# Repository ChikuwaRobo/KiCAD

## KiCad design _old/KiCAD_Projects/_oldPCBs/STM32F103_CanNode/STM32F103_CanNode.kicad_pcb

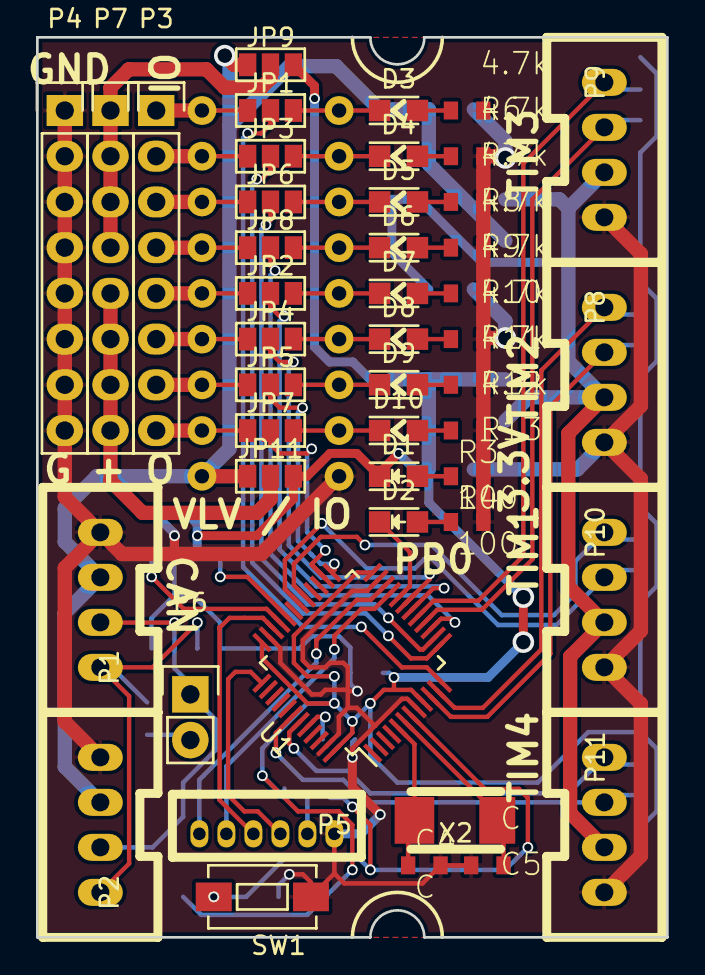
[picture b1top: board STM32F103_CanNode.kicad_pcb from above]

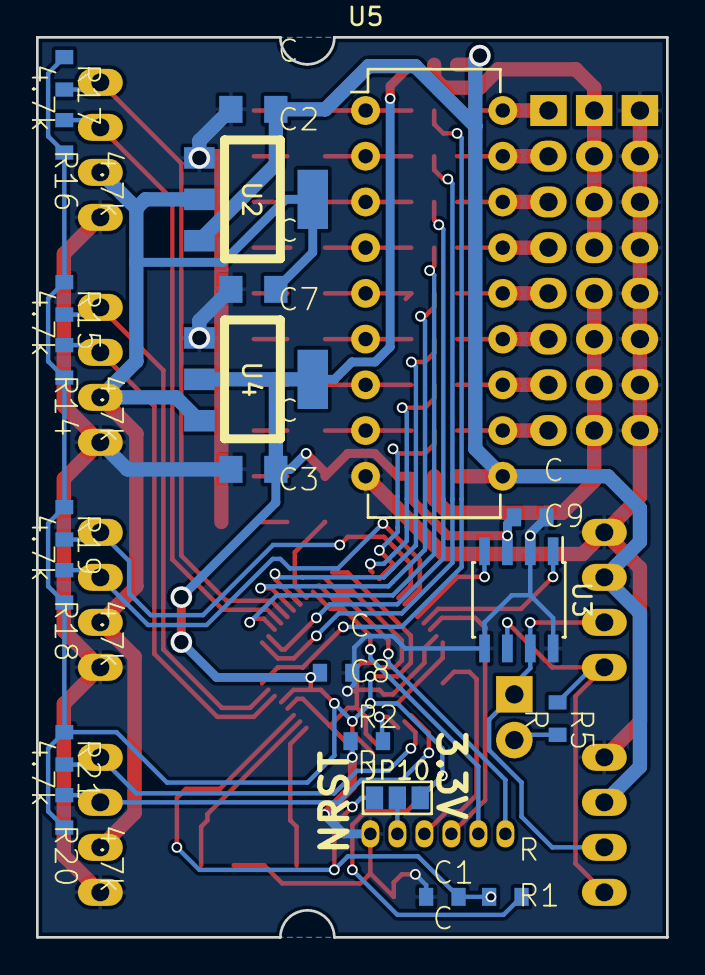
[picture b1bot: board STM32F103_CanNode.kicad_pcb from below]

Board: 2 copper layers, 35.0 x 50.0 mm, 68 parts (22 on the bottom side), 63 nets.

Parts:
C1, C4, C5, C8, C9: C; C1608_WP
C2, C3, C7: C; C2012
D1, D2, D3, D4, D5, D6, D7, D8, D9, D10: LED; LED_0805
JP1, JP2, JP3, JP4, JP5, JP6, JP7, JP8, JP9, JP10, JP11: JUMPER3; GS3
P1, P2, P8, P9, P10, P11: CONN_01X04; XA_4T
P3, P4, P7: CONN_01X08; Pin_Header_Straight_1x08
P5: CONN_01X06; ZH_6T
P6: CONN_01X02; Pin_Header_Straight_1x02
R1, R2, R5: R; C1608_WP
R3, R4: 100; C1608_WP
R6, R7, R8, R9, R10, R11, R12, R13, R14, R15, R16, R17, R18, R19, R20, R21: 4.7k; C1608_WP
SW1: SW_PUSH; SW_SPST_EVQPE1
U1: STM32F103_48; LQFP-48_7x7mm_Pitch0.5mm
U2: NCP1117ST33T3G; SOT-223_reg
U3: MAX3051; SOIC-8_3.9x4.9mm_Pitch1.27mm
U4: NCP1117ST50T3G; SOT-223_reg
U5: TBD62083A; DIP-18_W7.62mm
X2: CRYSTAL; ABM3_2pads

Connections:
+3.3V: C3.1, C8.2, C9.2, D1.1, JP9.3, JP10.3, JP11.3, R1.1, R14.1, R15.1, R16.1, R17.1, R18.1, R19.1, R20.1, R21.1, U1.9, U1.24, U1.36, U1.48, U3.3, U4.2
+5V: C7.1, P8.2, P9.2, P10.2, P11.2, U2.2, U4.3
+12V: C2.1, JP9.1, JP11.1, P1.2, P2.2, U2.3, U5.10
/BOOT0: R2.2, U1.44
/CAN_H: P1.3, P2.3, P6.1, U3.7
/CAN_L: P1.4, P2.4, R5.1, U3.6
/CAN_RX: U1.32, U3.4
/CAN_TX: U1.33, U3.1
/IO1: JP1.1, P3.1, U5.18
/IO2: JP3.1, P3.2, U5.17
/IO3: JP6.1, P3.3, U5.16
/IO4: JP8.1, P3.4, U5.15
/IO5: JP2.1, P3.5, U5.14
/IO6: JP4.1, P3.6, U5.13
/IO7: JP5.1, P3.7, U5.12
/IO8: JP7.1, P3.8, U5.11
/NRST: C1.2, JP10.1, R1.2, SW1.2, U1.7
/OSC_IN: C4.1, U1.5, X2.1
/OSC_OUT: C5.1, U1.6, X2.2
/OUT1: D3.1, JP1.3, U5.1
/OUT2: D4.1, JP3.3, U5.2
/OUT3: D5.1, JP6.3, U5.3
/OUT4: D6.1, JP8.3, U5.4
/OUT5: D7.1, JP2.3, U5.5
/OUT6: D8.1, JP4.3, U5.6
/OUT7: D9.1, JP5.3, U5.7
/OUT8: D10.1, JP7.3, U5.8
/PA0: P8.3, R14.2, U1.10
/PA1: P8.4, R15.2, U1.11
/PA2: JP1.2, U1.12
/PA3: JP3.2, U1.13
/PA4: JP6.2, U1.14
/PA5: JP8.2, U1.15
/PA6: P9.3, R16.2, U1.16
/PA7: P9.4, R17.2, U1.17
/PA8: P10.4, R19.2, U1.29
/PA9: P10.3, R18.2, U1.30
/PB0: JP2.2, U1.18
/PB1: JP4.2, U1.19
/PB2: D2.1, U1.20
/PB6: P11.3, R20.2, U1.42
/PB7: P11.4, R21.2, U1.43
/PB12: JP5.2, U1.25
/PB13: JP7.2, U1.26
/SWCLK: P5.3, U1.37
/SWDIO: P5.4, U1.34
/USART_RX: P5.6, U1.22
/USART_TX: P5.5, U1.21
GND: C1.1, C2.2, C3.2, C4.2, C5.2, C7.2, C8.1, C9.1, P1.1, P2.1, P4.1, P4.2, P4.3, P4.4, P4.5, P4.6, P4.7, P4.8, P5.1, P8.1, P9.1, P10.1, P11.1, R2.1, R3.2, R4.2, R6.1, R7.1, R8.1, R9.1, R10.1, R11.1, R12.1, R13.1, SW1.1, U1.8, U1.23, U1.35, U1.47, U2.1, U3.2, U3.5, U3.8, U4.1, U5.9
unnamed: D1.2, R3.1
unnamed: D2.2, R4.1
unnamed: D3.2, R6.2
unnamed: D4.2, R7.2
unnamed: D5.2, R8.2
unnamed: D6.2, R9.2
unnamed: D7.2, R10.2
unnamed: D8.2, R11.2
unnamed: D9.2, R12.2
unnamed: D10.2, R13.2
unnamed: JP9.2, P7.1, P7.2, P7.3, P7.4
unnamed: JP10.2, P5.2
unnamed: JP11.2, P7.5, P7.6, P7.7, P7.8
unnamed: P6.2, R5.2

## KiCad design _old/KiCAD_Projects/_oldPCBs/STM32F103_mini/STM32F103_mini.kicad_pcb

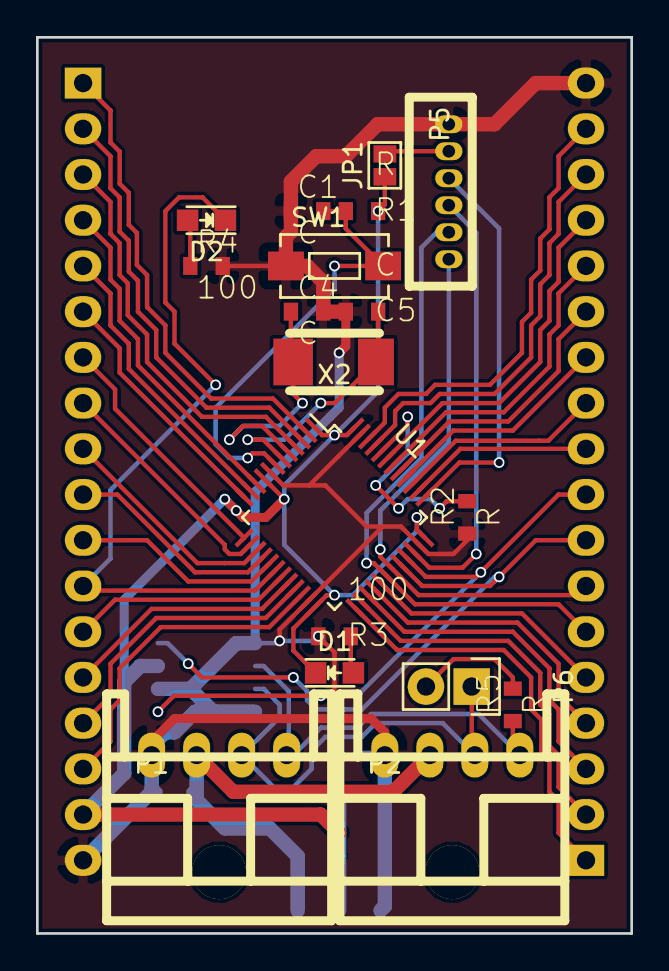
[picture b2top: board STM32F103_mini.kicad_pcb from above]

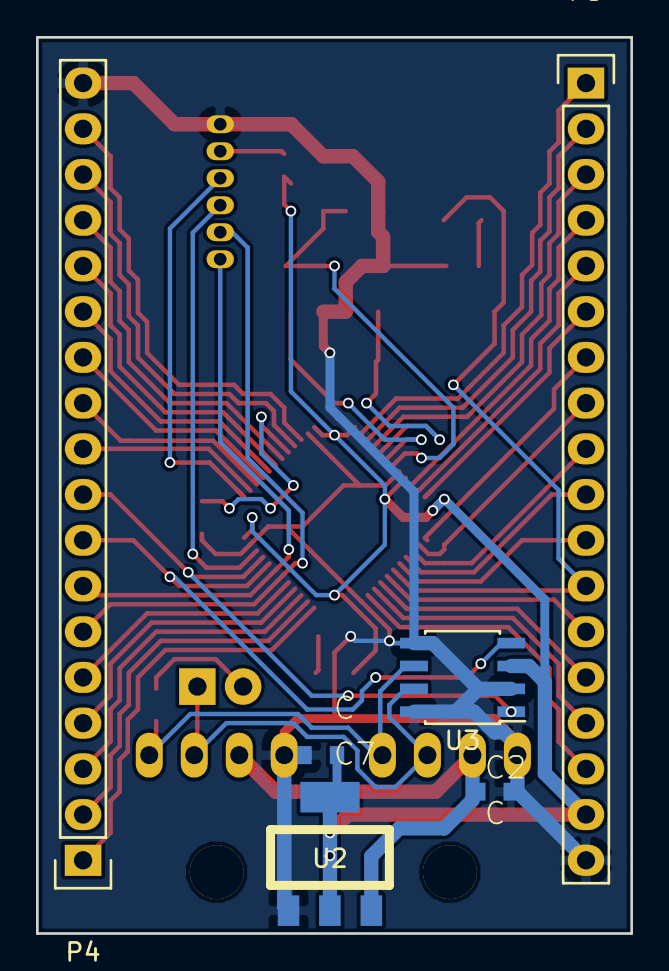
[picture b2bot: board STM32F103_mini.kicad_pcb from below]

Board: 2 copper layers, 33.0 x 49.8 mm, 24 parts (6 on the bottom side), 48 nets.

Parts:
C1, C2, C4, C5, C7: C; C1608_WP
D1, D2: LED; LED_0805
JP1: JUMPER; GS2
P1, P2: CONN_01X04; XA_4LC
P3, P4: CONN_01X18; Pin_Header_Straight_1x18
P5: CONN_01X06; ZH_6T
P6: CONN_01X02; Pin_Header_Straight_1x02
R1, R2, R5: R; C1608_WP
R3, R4: 100; C1608_WP
SW1: SW_PUSH; SW_SPST_EVQPE1
U1: STM32F103_48; LQFP-48_7x7mm_Pitch0.5mm
U2: NCP1117ST33T3G; SOT-223_reg
U3: MAX3051; SOIC-8_3.9x4.9mm_Pitch1.27mm
X2: CRYSTAL; ABM3_2pads

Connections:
+3V3: C7.1, D1.1, JP1.1, P3.17, R1.1, U1.1, U1.9, U1.24, U1.36, U1.48, U2.2, U3.3
+12V: C2.1, P1.2, P2.2, U2.3
/BOOT0: R2.2, U1.44
/CAN_H: P1.3, P2.3, P6.1, U3.7
/CAN_L: P1.4, P2.4, R5.1, U3.6
/CAN_RX: P4.8, U1.32, U3.4
/CAN_TX: P4.9, U1.33, U3.1
/LED: D2.1, P3.12, U1.18
/NRST: C1.2, R1.2, SW1.2, U1.7
/OSC_IN: C4.1, U1.5, X2.1
/OSC_OUT: C5.1, U1.6, X2.2
/PA0: P3.4, U1.10
/PA1: P3.5, U1.11
/PA2: P3.6, U1.12
/PA3: P3.7, U1.13
/PA4: P3.8, U1.14
/PA5: P3.9, U1.15
/PA6: P3.10, U1.16
/PA7: P3.11, U1.17
/PA8: P4.5, U1.29
/PA15: P4.10, U1.38
/PB1: P3.13, U1.19
/PB2: P3.14, U1.20
/PB3: P4.11, U1.39
/PB4: P4.12, U1.40
/PB5: P4.13, U1.41
/PB6: P4.14, U1.42
/PB7: P4.15, U1.43
/PB8: P4.16, U1.45
/PB9: P4.17, U1.46
/PB10: P3.15, U1.21
/PB11: P3.16, U1.22
/PB12: P4.1, U1.25
/PB13: P4.2, U1.26
/PB14: P4.3, U1.27
/PB15: P4.4, U1.28
/PC13: P3.1, U1.2
/PC14: P3.2, U1.3
/PC15: P3.3, U1.4
/SWCLK: P5.3, U1.37
/SWDIO: P5.4, U1.34
/USART_RX: P4.7, P5.6, U1.31
/USART_TX: P4.6, P5.5, U1.30
GND: C1.1, C2.2, C4.2, C5.2, C7.2, P1.1, P2.1, P3.18, P4.18, P5.1, R2.1, R3.2, R4.2, SW1.1, U1.8, U1.23, U1.35, U1.47, U2.1, U3.2, U3.5, U3.8
unnamed: D1.2, R3.1
unnamed: D2.2, R4.1
unnamed: JP1.2, P5.2
unnamed: P6.2, R5.2

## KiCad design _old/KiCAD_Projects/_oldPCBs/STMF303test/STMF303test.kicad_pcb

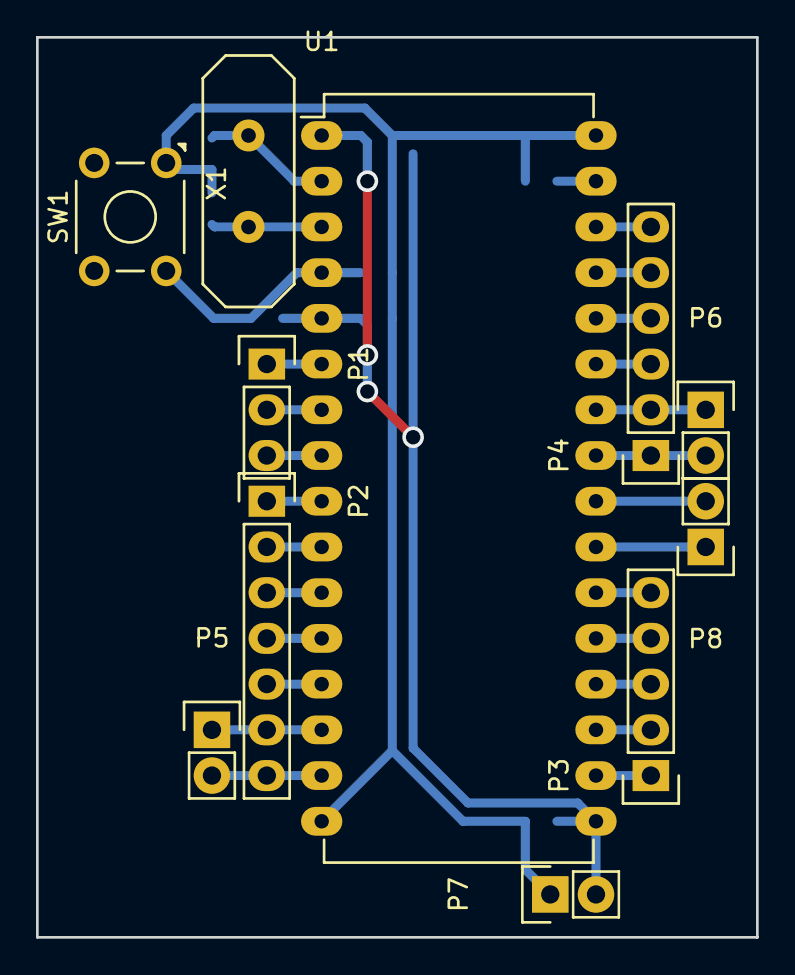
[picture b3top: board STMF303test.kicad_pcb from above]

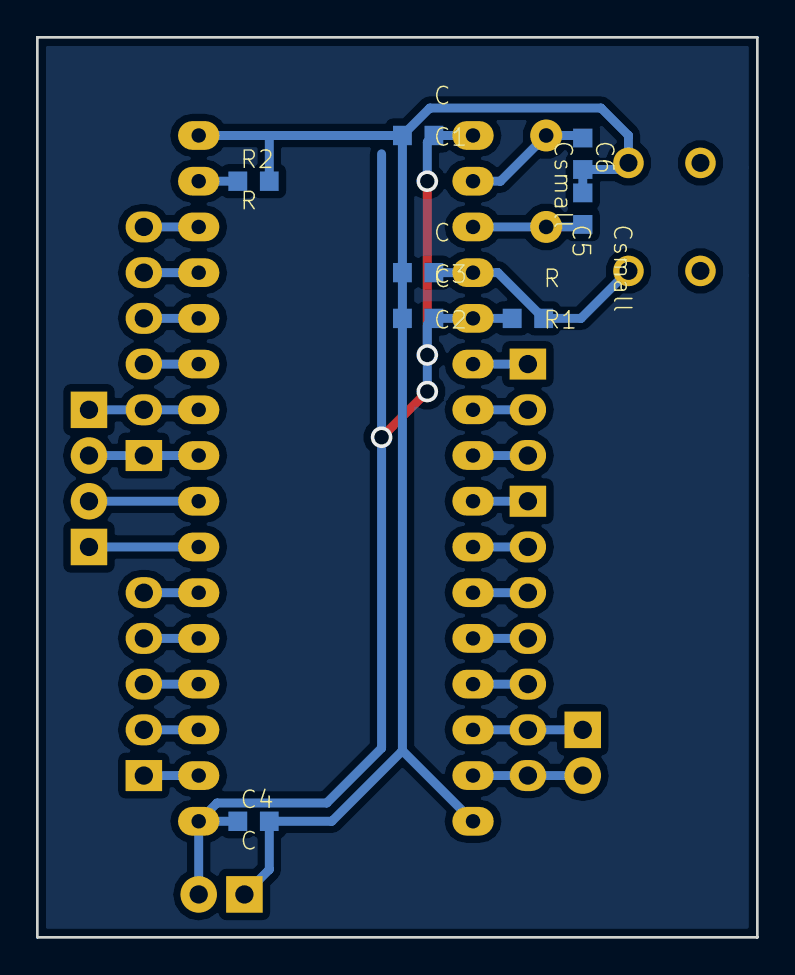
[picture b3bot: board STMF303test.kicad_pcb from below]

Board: 2 copper layers, 40.0 x 50.0 mm, 19 parts (8 on the bottom side), 29 nets.

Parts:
C1, C2, C3, C4: C; C0603K
C5, C6: Csmall; C0603K
P1: CONN_01X03; Socket_Strip_Straight_1x03
P2: CONN_01X07; Socket_Strip_Straight_1x07
P3: CONN_01X05; Socket_Strip_Straight_1x05
P4: CONN_01X06; Socket_Strip_Straight_1x06
P5, P6, P7, P8: CONN_01X02; Pin_Header_Straight_1x02
R1, R2: R; C0603K
SW1: SW_PUSH; SW_TH_Tactile_Omron_B3F-10xx
U1: STM32F303K8; DIP-32_W15.24mm_LongPads
X1: CRYSTAL; HC-18UV

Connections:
+3.3V: C1.1, C2.1, C4.1, P7.2, R1.2, U1.1, U1.5, U1.17
/PIN6: P1.1, U1.6
/PIN7: P1.2, U1.7
/PIN8: P1.3, U1.8
/PIN9: P2.1, U1.9
/PIN10: P2.2, U1.10
/PIN11: P2.3, U1.11
/PIN12: P2.4, U1.12
/PIN13: P2.5, U1.13
/PIN14: P2.6, P5.1, U1.14
/PIN15: P2.7, P5.2, U1.15
/PIN18: P3.1, U1.18
/PIN19: P3.2, U1.19
/PIN20: P3.3, U1.20
/PIN21: P3.4, U1.21
/PIN22: P3.5, U1.22
/PIN25: P4.1, P6.2, U1.25
/PIN26: P4.2, P6.1, U1.26
/PIN27: P4.3, U1.27
/PIN28: P4.4, U1.28
/PIN29: P4.5, U1.29
/PIN30: P4.6, U1.30
/SWCLK: P8.2, U1.24
/SWDIO: P8.1, U1.23
GND: C1.2, C2.2, C3.2, C4.2, C5.2, C6.2, P7.1, R2.2, SW1.1, U1.16, U1.32
unnamed: C3.1, R1.1, SW1.2, U1.4
unnamed: C5.1, U1.3, X1.1
unnamed: C6.1, U1.2, X1.2
unnamed: R2.1, U1.31

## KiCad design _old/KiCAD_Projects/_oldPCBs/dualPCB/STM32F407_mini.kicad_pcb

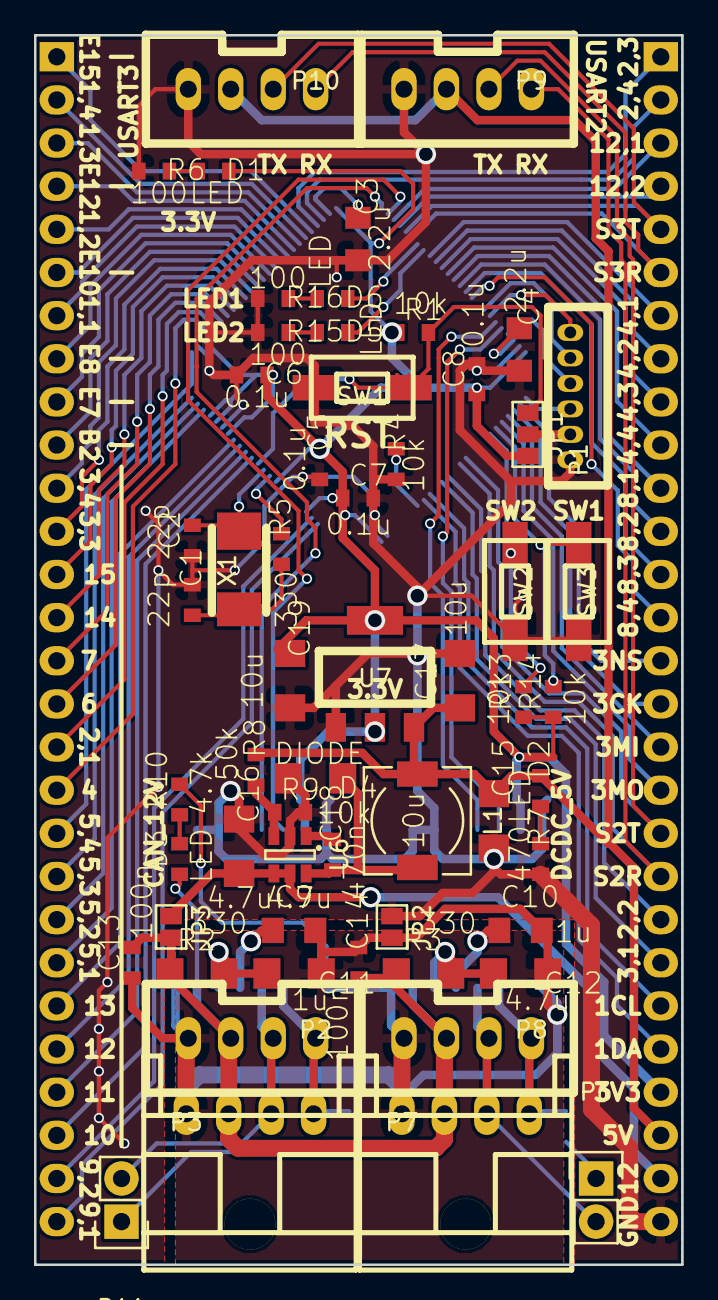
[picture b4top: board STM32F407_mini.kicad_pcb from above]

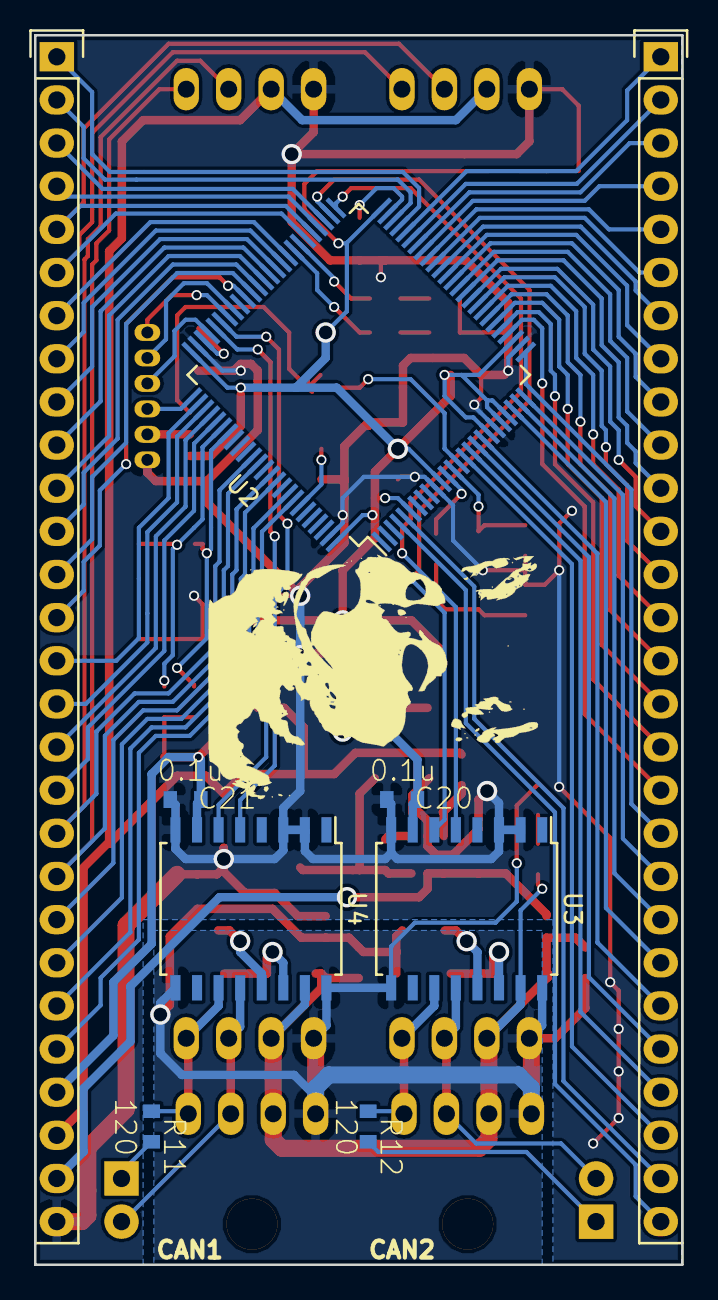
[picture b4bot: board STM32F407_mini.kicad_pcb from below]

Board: 2 copper layers, 38.1 x 72.4 mm, 67 parts (9 on the bottom side), 96 nets.

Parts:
C1, C2: 22p; C1608_WP
C3, C4: 2.2u; C2012
C5, C6, C7, C8, C20, C21: 0.1u; C1608_WP
C9, C10: 1u; C2012
C11, C12, C16: 4.7u; C3216
C13, C14: 100n; C1608_WP
C15, C17, C19: 10u; C3216
C18: 470n; C1608_WP
D1, D2, D3, D5, D6: LED; C1608_WP
D4: DIODE; C3216
JP1: JUMPER3; GS3
JP2, JP3: JUMPER; GS2
L1: 2.2uH; Choke_SMD_6.3x6.3_H3
P1: CONN_01X06; ZH_6T
P2, P8, P9, P10: CONN_01X04; XA_4T
P3, P7: CONN_01X04; XA_4LC
P4, P5: CONN_01X28; Pin_Header_Straight_1x28
P6, P11: CONN_01X02; Pin_Header_Straight_1x02
R1, R4, R9, R13, R14: 10k; C1608_WP
R2, R3: 330; C3216
R5: 330; C1608_WP
R6, R15, R16: 100; C1608_WP
R7: 470; C1608_WP
R8: 50k; C1608_WP
R10: 4.7k; C1608_WP
R11, R12: 120; C1608_WP
SW1, SW2, SW3: SW_PUSH; RP_SMD_Button
U2: STM32F407VG; LQFP-100_14x14mm_Pitch0.5mm
U3, U4: ADM3052; SOIC-16_7.5x10.3mm_Pitch1.27mm
U6: AOZ1280; SOT-23-6
U7: NCP1117ST33T3G; SOT-223_reg
X1: CRYSTAL; ABM3_2pads

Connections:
+3.3V: C5.1, C6.1, C7.1, C8.1, C19.1, C20.1, C21.1, D1.1, JP1.3, P5.25, R1.1, R13.1, R14.1, U2.6, U2.11, U2.19, U2.21, U2.22, U2.28, U2.50, U2.75, U2.100, U3.7, U4.7, U7.2
+5V: C15.1, C17.1, D2.1, L1.1, P5.26, P9.2, P10.2, R8.1, U7.3
+12V: C16.2, JP3.1, P5.27, U6.4, U6.5
/ADC1_6: P4.16, U2.31
/ADC1_7: P4.15, U2.32
/ADC1_IN4: P4.18, U2.29
/ADC_IN10: P4.26, U2.15
/ADC_IN11: P4.25, U2.16
/ADC_IN12: P4.24, U2.17
/ADC_IN13: P4.23, U2.18
/ADC_IN14: P4.14, U2.33
/ADC_IN15: P4.13, U2.34
/BOOT0: R4.1, U2.94
/CAN1_H: P6.2, P7.3, P8.3, U4.12
/CAN1_L: P7.4, P8.4, R11.1, U4.11
/CAN1_RX: U2.70, U4.5
/CAN1_TX: U2.71, U4.6
/CAN2_H: P2.3, P3.3, P11.2, U3.12
/CAN2_L: P2.4, P3.4, R12.1, U3.11
/CAN2_RX: U2.51, U3.5
/CAN2_TX: U2.52, U3.6
/CAN_12V: C13.2, C14.2, D3.1, JP3.2, P2.2, P3.2, P7.2, P8.2, R2.1, R3.1, U3.15, U4.15
/DCDC_FB: R8.2, R9.1, U6.3
/GPIO_PB2: P4.10, U2.37
/GPIO_PE7: P4.9, U2.38
/GPIO_PE8: P4.8, U2.39
/GPIO_PE10: P4.6, U2.41
/GPIO_PE12: P4.4, U2.43
/GPIO_PE15: P4.1, U2.46
/I2C1_SCL: P5.23, U2.92
/I2C1_SDA: P5.24, U2.93
/LED1: D6.1, U2.57
/LED2: D5.1, U2.58
/NRST: JP1.1, R1.2, SW1.1, U2.14
/SPI3_MISO: P5.17, U2.79
/SPI3_MOSI: P5.18, U2.80
/SPI3_NSS: P5.15, U2.77
/SPI3_SCK: P5.16, U2.78
/SW1_IN: R14.2, SW3.1, U2.81
/SW2_IN: R13.2, SW2.1, U2.82
/SWDCK: P1.3, U2.76
/SWDIO: P1.4, U2.72
/TIM1_CH1: P4.7, U2.40
/TIM1_CH2: P4.5, U2.42
/TIM1_CH3: P4.3, U2.44
/TIM1_CH4: P4.2, U2.45
/TIM2_CH1: P4.17, U2.30
/TIM2_CH2: P5.21, U2.89
/TIM2_CH3: P5.1, U2.47
/TIM2_CH4: P5.2, U2.48
/TIM3_CH1: P5.22, U2.90
/TIM3_CH3: P4.12, U2.35
/TIM3_CH4: P4.11, U2.36
/TIM4_CH1: P5.7, U2.59
/TIM4_CH2: P5.8, U2.60
/TIM4_CH3: P5.9, U2.61
/TIM4_CH4: P5.10, U2.62
/TIM5_CH1: P4.22, U2.23
/TIM5_CH2: P4.21, U2.24
/TIM5_CH3: P4.20, U2.25
/TIM5_CH4: P4.19, U2.26
/TIM8_CH1: P5.11, U2.63
/TIM8_CH2: P5.12, U2.64
/TIM8_CH3: P5.13, U2.65
/TIM8_CH4: P5.14, U2.66
/TIM9_CH1: P4.28, U2.4
/TIM9_CH2: P4.27, U2.5
/TIM12_CH1: P5.3, U2.53
/TIM12_CH2: P5.4, U2.54
/USART1_RX: P1.6, U2.69
/USART1_TX: P1.5, U2.68
/USART2_RX: P5.20, P9.4, U2.87
/USART2_TX: P5.19, P9.3, U2.86
/USART3_RX: P5.6, P10.4, U2.56
/USART3_TX: P5.5, P10.3, U2.55
DGND: C9.2, C10.2, C11.1, C12.1, C13.1, C14.1, JP2.2, P2.1, P3.1, P7.1, P8.1, R10.2, U3.9, U3.16, U4.9, U4.16
GND: C1.1, C2.1, C3.2, C4.2, C5.2, C6.2, C7.2, C8.2, C15.2, C16.1, C17.2, C19.2, C20.2, C21.2, D4.2, JP2.1, P1.1, P5.28, P9.1, P10.1, R4.2, R6.2, R7.2, R9.2, R15.2, R16.2, SW1.2, SW2.2, SW3.2, U2.10, U2.20, U2.27, U2.74, U2.99, U3.2, U3.3, U3.8, U4.2, U4.3, U4.8, U6.2, U7.1
unnamed: C1.2, R5.2, X1.2
unnamed: C2.2, U2.13, X1.1
unnamed: C3.1, U2.49
unnamed: C4.1, U2.73
unnamed: C9.1, U3.13
unnamed: C10.1, U4.13
unnamed: C11.2, R2.2, U3.14
unnamed: C12.2, R3.2, U4.14
unnamed: C18.1, U6.1
unnamed: C18.2, D4.1, L1.2, U6.6
unnamed: D1.2, R6.1
unnamed: D2.2, R7.1
unnamed: D3.2, R10.1
unnamed: D5.2, R15.1
unnamed: D6.2, R16.1
unnamed: JP1.2, P1.2
unnamed: P6.1, R11.2
unnamed: P11.1, R12.2
unnamed: R5.1, U2.12

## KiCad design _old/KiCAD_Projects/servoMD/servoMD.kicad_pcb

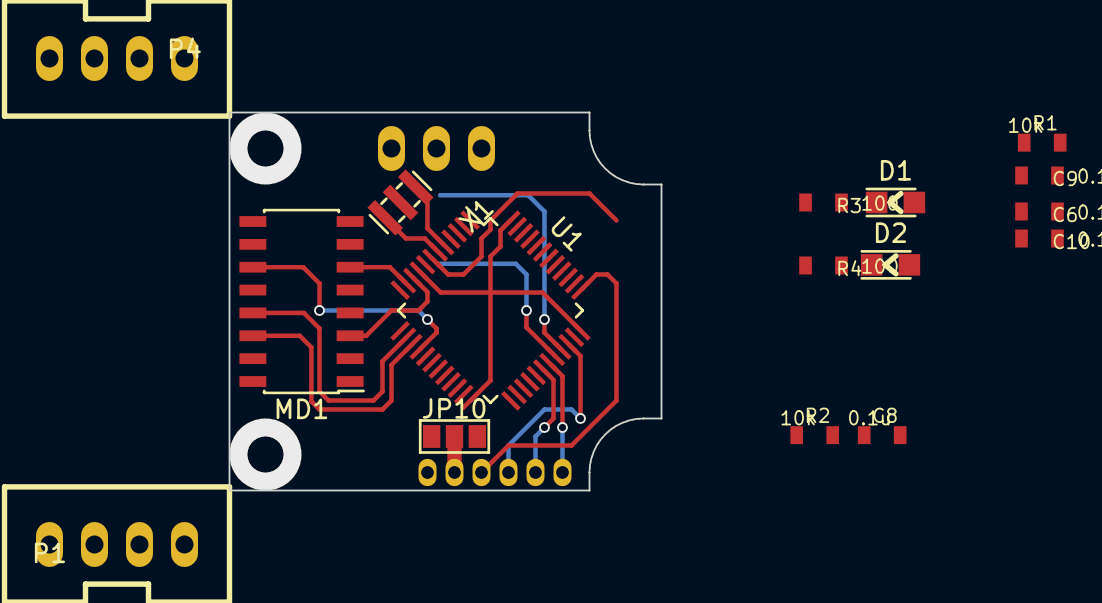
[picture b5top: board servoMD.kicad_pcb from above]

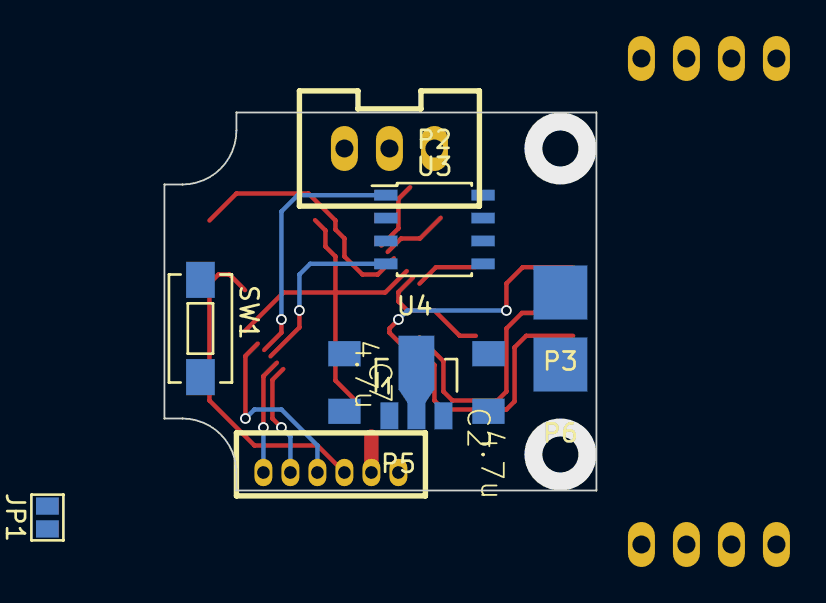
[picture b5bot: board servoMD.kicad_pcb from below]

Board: 2 copper layers, 24.0 x 21.0 mm, 26 parts (10 on the bottom side), 28 nets.

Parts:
C2, C7: 4.7u; C3216_S
C6, C8, C9, C10: 0.1u; C1608_WP_S
D1, D2: LED; LED_0805
JP1: JUMPER; GS2
JP10: JUMPER3; GS3
MD1: VNH7100AS; SOIC-16_3.9x9.9mm_Pitch1.27mm
P1, P4: CONN_01X04; XA_4T
P2: CONN_01X03; XA_3T
P3, P6: CONN_01X01; Measurement_Point_Square-SMD-Pad_Big
P5: CONN_01X06; ZH_6T
R1, R2: 10k; C1608_WP_S
R3, R4: 100; C1608_WP_S
SW1: SW_PUSH; SW_SPST_EVQPE1
U1: STM32F103_48; LQFP-48_7x7mm_Pitch0.5mm
U3: MAX3051; SOIC-8_3.9x4.9mm_Pitch1.27mm_S
U4: NCP1117ST50T3G; SOT89-3_Housing
X1: ceralock; Resonator_3×1.3mm

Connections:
+3.3V: C6.2, C7.1, C8.2, C9.2, C10.2, D1.1, JP10.3, P2.2, R1.1, U1.9, U1.24, U1.36, U1.48, U3.3, U4.2
+5V: JP10.1, P1.2
+12V: C2.1, MD1.4, MD1.5, MD1.12, U4.3
/BOOT0: R2.2, U1.44
/CAN_H: P4.3, U3.7
/CAN_L: P4.4, U3.6
/CAN_RX: U1.32, U3.4
/CAN_TX: U1.33, U3.1
/CS: MD1.13, U1.14
/INA: MD1.3, U1.10
/INB: MD1.6, U1.11
/NRST: R1.2, SW1.2, U1.7
/OSC_IN: U1.5, X1.1
/OSC_OUT: U1.6, X1.3
/OUTA: MD1.2, MD1.15, P3.1
/OUTB: MD1.7, MD1.10, P6.1
/POT: P2.3, U1.12
/PWM: MD1.11, U1.16
/SEL: MD1.14, U1.15
/SWCLK: P5.3, U1.37
/SWDIO: P5.4, U1.34
/USART_RX: P5.6, U1.31
/USART_TX: P5.5, U1.30
DGND: JP1.1, P4.1
GND: C2.2, C6.1, C7.2, C8.1, C9.1, C10.1, JP1.2, MD1.1, MD1.8, MD1.9, MD1.16, P1.1, P2.1, P5.1, R2.1, R3.2, R4.2, SW1.1, U1.8, U1.23, U1.35, U1.47, U3.2, U3.5, U3.8, U4.1, X1.2
unnamed: D1.2, R3.1
unnamed: D2.2, R4.1
unnamed: JP10.2, P5.2

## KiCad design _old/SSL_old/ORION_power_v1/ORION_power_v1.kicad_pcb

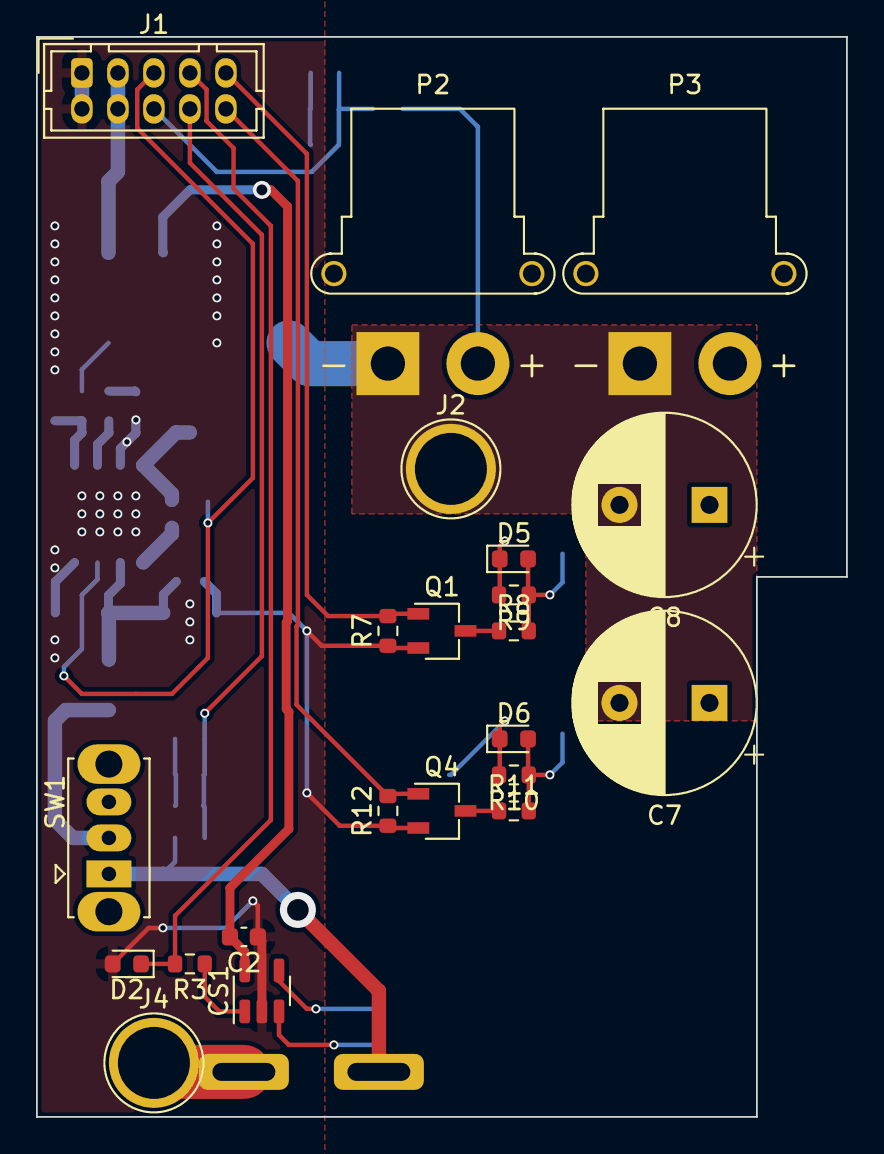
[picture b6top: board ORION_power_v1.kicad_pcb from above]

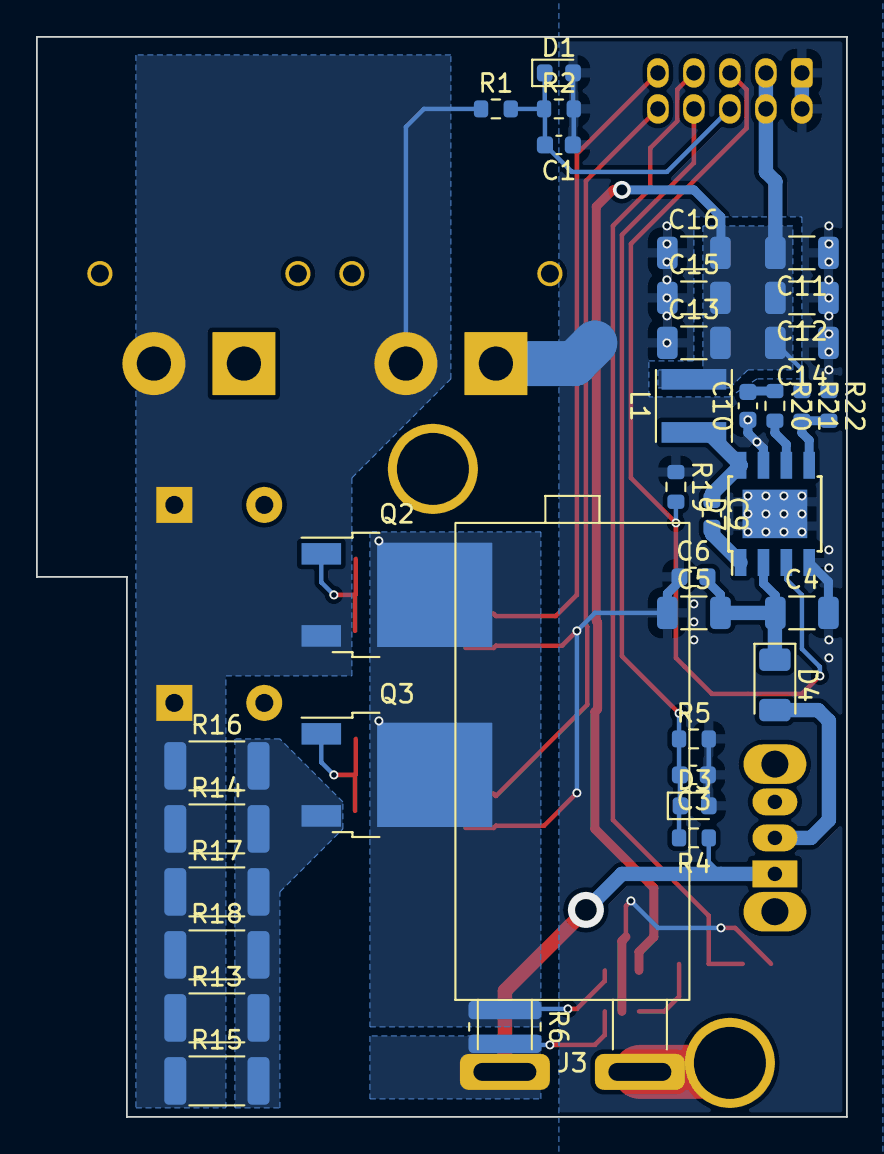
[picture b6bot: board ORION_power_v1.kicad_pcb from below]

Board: 2 copper layers, 45.0 x 60.0 mm, 58 parts (36 on the bottom side), 25 nets.

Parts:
C1, C2, C3, C6, C9: 0.1u; C_0603_1608Metric
C4, C5, C11, C12, C13, C14, C15, C16: 4.7u; C_1206_3216Metric
C7, C8: 470u; CP_Radial_D10.0mm_P5.00mm
C10: 1300p; C_0603_1608Metric
CS1: CS30; SOT-23-5
D1, D2, D3: D_Zener_3.3V; D_0603_1608Metric
D4: D; D_1206_3216Metric
D5, D6: D_Zener_12V; D_0603_1608Metric
D7: BD9E302EFJ; Diodes_PSOP-8
J1: Conn_02x05_Odd_Even; Hirose_DF11-10DP-2DSA_2x05_P2.00mm_Vertical
J2, J4: Conn_01x01; TestPoint_Plated_Hole_D4.0mm
J3: Conn_01x02; Reusable_Breaker
L1: 10uH; L_Vishay_IFSC-1515AH_4x4x1.8mm
P2, P3: CONN_01X02; AMASS_XT30PW-F_1x02_P2.50mm_Horizontal
Q1, Q4: Q_NMOS_GSD; TSOT-23
Q2, Q3: Q_PMOS_GDS; TO-252-2
R1, R4: 10k; R_0603_1608Metric
R2, R5, R7, R9, R10, R12, R19, R22: 1k; R_0603_1608Metric
R3, R8, R11: 100; R_0603_1608Metric
R6: 1m; R_0815_2038Metric
R13, R14, R15, R16, R17, R18: 1k; R_2010_5025Metric
R20: 6k; R_0603_1608Metric
R21: 15k; R_0603_1608Metric
SW1: SW_SPST_Temperature; SW_Slide_1P2T_CK_OS102011MS2Q

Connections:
+5V: C2.2, C11.2, C12.2, C13.2, C14.2, C15.2, C16.2, CS1.5 (VCC), J1.3, J1.4, L1.2, R21.1
+BATT: CS1.3 (Vp), J3.1, R4.1, R6.2, SW1.1 (A)
/BattVsense: C3.2, D3.1 (K), J1.8, R4.2, R5.1
/CurrentSense: D2.1 (K), J1.7, R3.2
/DCDC_5V_EN: D7.3 (EN), J1.5, R19.2
/PRE_CHARGE_EN: J1.10, Q4.1 (G), R12.2
/PW_OUT: C7.1, C8.1, P2.2, P3.2, Q2.3 (S), R1.1, R13.1, R14.1, R15.1, R16.1, R17.1, R18.1
/PW_OUT_EN: J1.9, Q1.1 (G), R7.2
/PowerOutVSense: C1.2, D1.1 (K), J1.6, R1.2, R2.1
GND: C1.1, C2.1, C3.1, C4.2, C5.1, C6.1, C7.2, C8.2, C10.1, C11.1, C12.1, C13.1, C14.1, C15.1, C16.1, CS1.2 (GND), D1.2 (A), D2.2 (A), D3.2 (A), D7.4 (AGND), D7.7 (PGND), D7.9 (PAD), J1.1, J1.2, J2.1, P2.1, P3.1, Q1.2 (S), Q4.2 (S), R2.2, R5.2, R7.1, R12.1, R19.1, R22.1
unnamed: C4.1, C5.2, C6.2, D4.1 (K), D7.2 (VIN)
unnamed: C9.1, D7.8 (SW), L1.1
unnamed: C9.2, D7.1 (BOOT)
unnamed: C10.2, R20.1
unnamed: CS1.1 (OUT), R3.1
unnamed: CS1.4 (Vm), D5.1 (K), D6.1 (K), Q2.2 (D), Q3.2 (D), R6.1, R9.2, R10.2
unnamed: D4.2 (A), SW1.2 (B)
unnamed: D5.2 (A), Q2.1 (G), R8.2, R9.1
unnamed: D6.2 (A), Q3.1 (G), R10.1, R11.2
unnamed: D7.5 (FB), R21.2, R22.2
unnamed: D7.6 (COMP), R20.2
unnamed: J3.2, J4.1
unnamed: Q1.3 (D), R8.1
unnamed: Q3.3 (S), R13.2, R14.2, R15.2, R16.2, R17.2, R18.2
unnamed: Q4.3 (D), R11.1

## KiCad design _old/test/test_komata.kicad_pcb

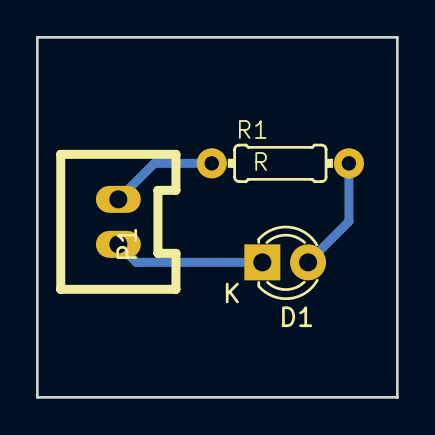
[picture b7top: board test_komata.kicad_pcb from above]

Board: 2 copper layers, 20.0 x 20.0 mm, 3 parts (0 on the bottom side), 3 nets.

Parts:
D1: LED; LED-3MM
P1: CONN_01X02; XA_2T
R1: R; 0204_2f7

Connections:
+2V5: P1.1, R1.1
GND: D1.1, P1.2
unnamed: D1.2, R1.2
